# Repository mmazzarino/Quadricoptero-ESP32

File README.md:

### Atenção: 

#### Este repositório é antigo e está muito desatualizado. Em breve o repositório que contém os códigos atuais do Quadricoptero-ESP32 passará de privado para público.

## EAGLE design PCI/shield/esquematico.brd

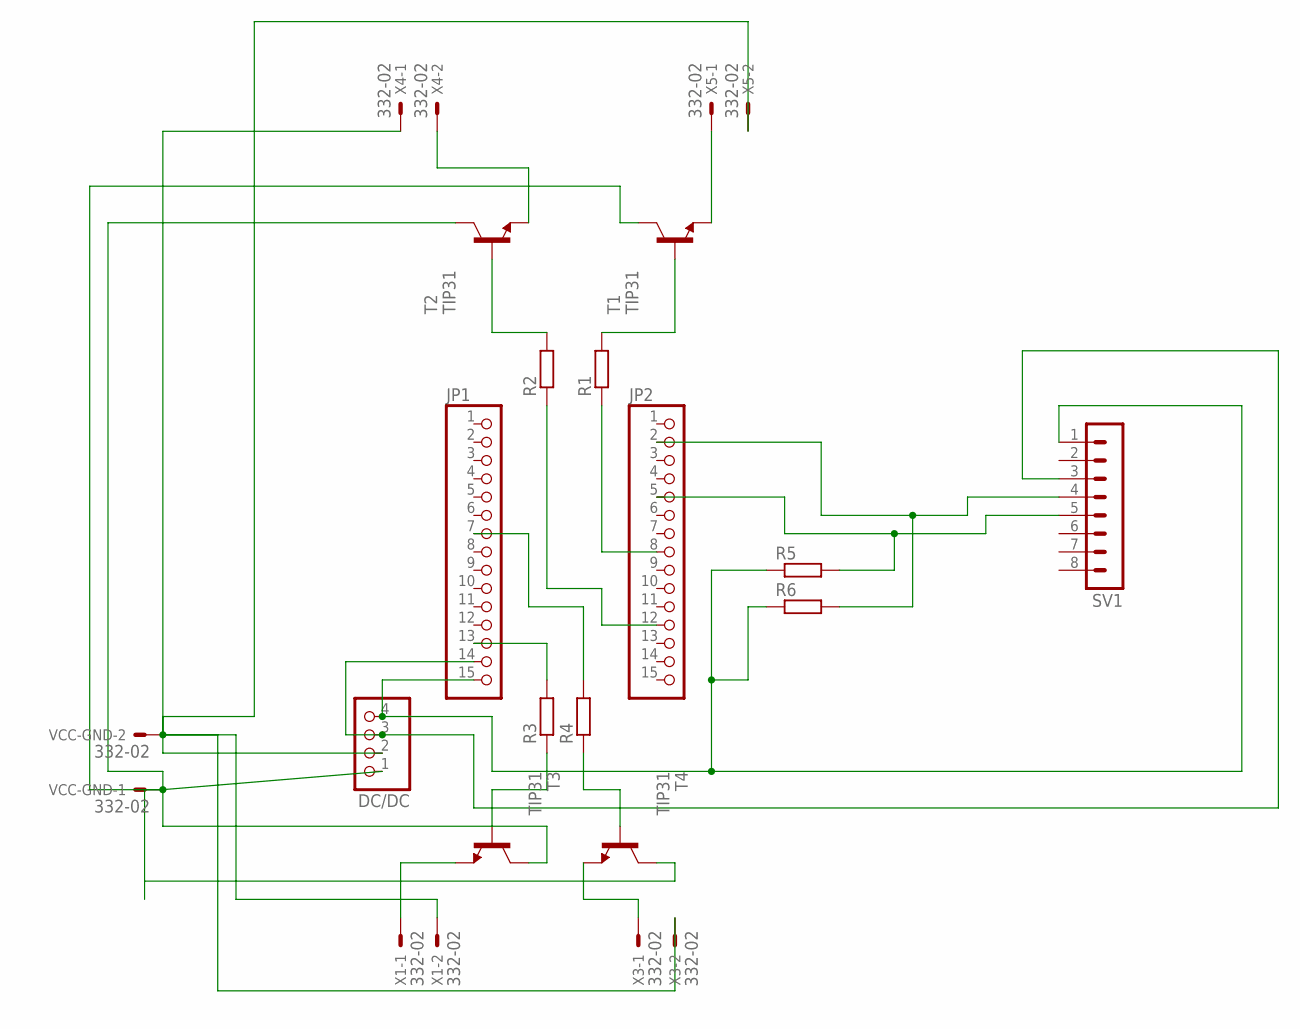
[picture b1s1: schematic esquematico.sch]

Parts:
DC/DC: PINHD-1X4; 1X04
JP1, JP2: PINHD-1X15; 1X15
R1, R2, R3, R4, R5, R6: R0207/10; 0207/10
SV1: MA08-1
T1, T2, T3, T4: TIP31; TO220
VCC-GND: 332-02
X1, X3, X4, X5: 332-02

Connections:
unnamed: JP1.13, R3.2
unnamed: JP2.12, R2.1
unnamed: JP2.8, R1.1
unnamed: R4.1, T4.1 (B)
unnamed: R3.1, T3.1 (B)
unnamed: R1.2, T1.1 (B)
unnamed: R2.2, T2.1 (B)
unnamed: T3.3 (E), X1.1
unnamed: JP2.2, R6.2, SV1.4
unnamed: JP2.5, R5.2, SV1.5
unnamed: DC/DC.4, JP1.15, R5.1, R6.1, SV1.1
unnamed: DC/DC.1, T1.2 (C), T2.2 (C), T3.2 (C), T4.2 (C), VCC-GND.1
unnamed: JP1.7, R4.2
unnamed: DC/DC.3, JP1.14, SV1.3
unnamed: DC/DC.2, VCC-GND.2, X1.2, X3.2, X4.1, X5.2
unnamed: T4.3 (E), X3.1
unnamed: T2.3 (E), X4.2
unnamed: T1.3 (E), X5.1

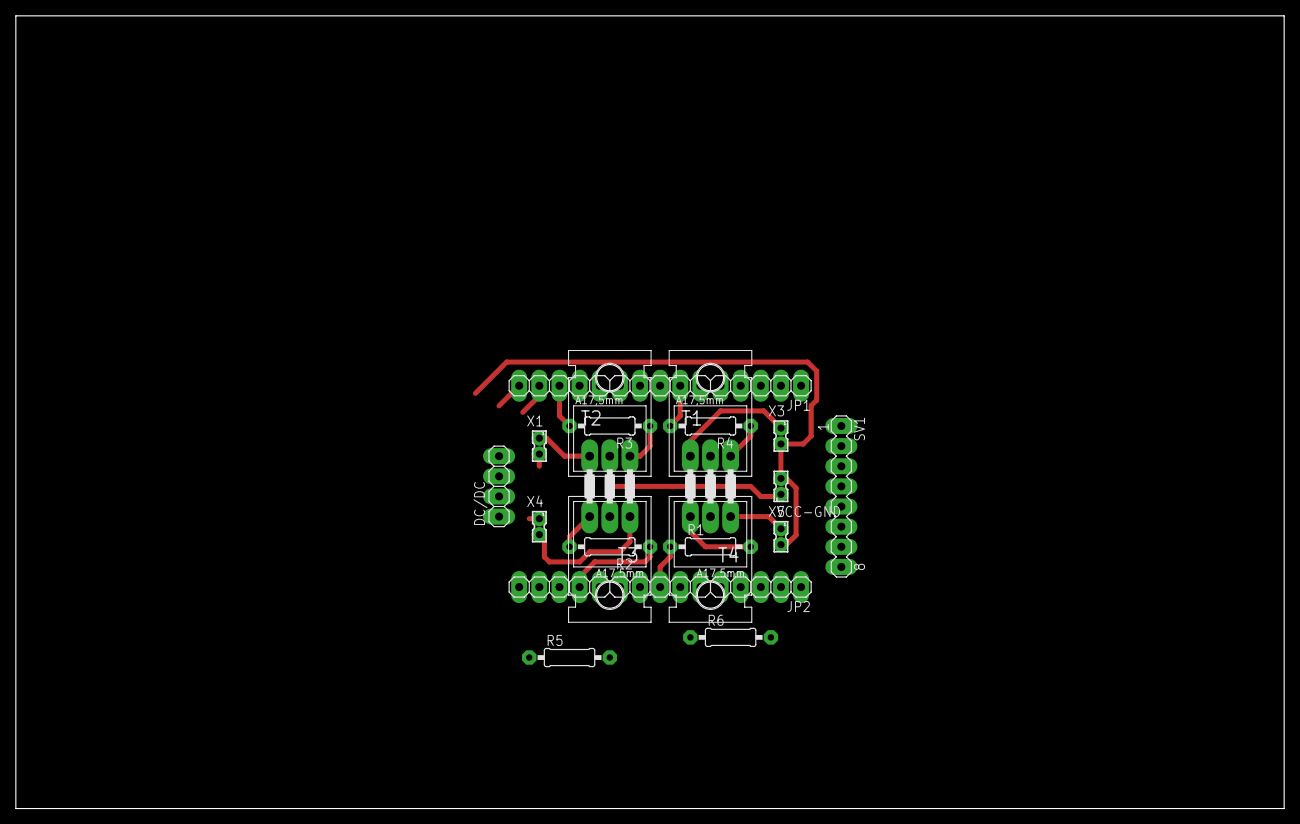
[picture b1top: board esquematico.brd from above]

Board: 2 copper layers, 160.0 x 100.0 mm, 19 parts (0 on the bottom side), 18 nets.

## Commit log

2019-03-21 blabla
2019-03-22 continuando
2019-03-27 Iniciando a biblioteca para controle pid dos motores
2019-03-28 Continuação binlioteca
2019-03-29 continuação
2019-06-05 Comecando integracao
2019-06-06 mais um dia
2019-06-07 fazendo teste
2019-06-11 teste
2019-06-13 manipulacao de arquivos
2019-06-17 ta fluindo
2019-06-18 configura saida dos dados do mpu em json
2019-06-18 tete
2019-06-19 continuani
2019-06-24 configurações pid
2019-06-27 edĩções nas configuracoes
2019-06-27 Teste MPU bombou com resistores de pull up
2019-06-28 compilando
2019-07-30 modificações basicas
2019-10-21 atualiza
2019-12-09 organizacao pastas
2019-12-09 datasheets + esquematico
2019-12-09 aatualiza
2019-12-10 fazendo frame
2019-12-11 frame pronto
2020-02-05 Desenvolvimento inicial do protocolo DSHOT
2020-02-13 Ajustando valores do DSHOT 600 para clock de 240MHz
2020-02-14 aplicação da biblioteca do MPU 9250
2020-02-20 integracao.txt
2021-01-08 Atualizacao do repositorio
